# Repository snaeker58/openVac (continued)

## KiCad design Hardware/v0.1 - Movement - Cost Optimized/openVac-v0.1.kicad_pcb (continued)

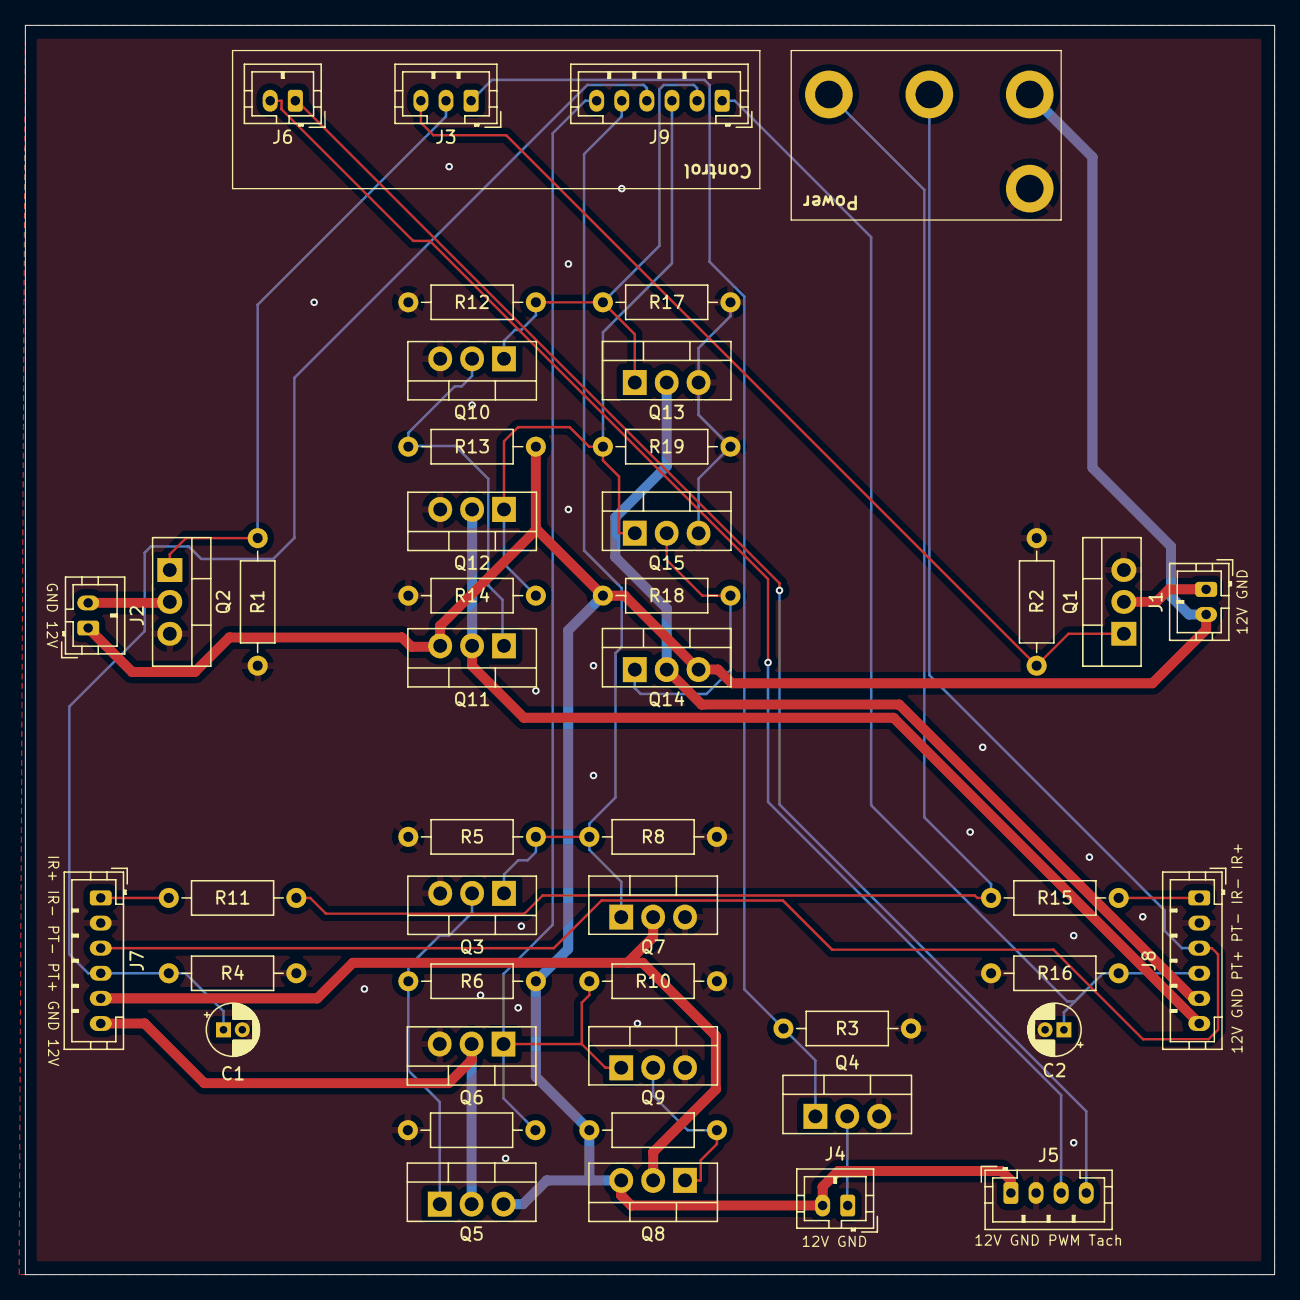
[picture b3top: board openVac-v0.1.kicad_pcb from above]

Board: 2 copper layers, 99.5 x 99.5 mm, 49 parts (0 on the bottom side), 28 nets.

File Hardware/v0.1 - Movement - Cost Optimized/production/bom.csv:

Designator,Footprint,Quantity,Value,LCSC Part #
"C1, C2",CP_Radial_D4.0mm_P1.50mm,2,0.1uF,
J1,JST_PH_B2B-PH-K_1x02_P2.00mm_Vertical,1,Brush Motor 2 (right),
J2,JST_PH_B2B-PH-K_1x02_P2.00mm_Vertical,1,Brush Motor 1 (left),
J3,JST_PH_B3B-PH-K_1x03_P2.00mm_Vertical,1,Brush Header (control),
J4,JST_PH_B2B-PH-K_1x02_P2.00mm_Vertical,1,Brush Motor Main,
J5,JST_PH_B4B-PH-K_1x04_P2.00mm_Vertical,1,Vacuum,
J6,JST_PH_B2B-PH-K_1x02_P2.00mm_Vertical,1,Vacuum Header (control),
J7,JST_PH_B6B-PH-K_1x06_P2.00mm_Vertical,1,Motor (left),
J8,JST_PH_B6B-PH-K_1x06_P2.00mm_Vertical,1,Motor (right),
J9,JST_PH_B6B-PH-K_1x06_P2.00mm_Vertical,1,Motor Header (control),
"Q1, Q10, Q12, Q13, Q15, Q2, Q3, Q4, Q6, Q7, Q9",TO-220-3_Vertical,11,IRF540N,
"Q11, Q14, Q5, Q8",TO-220-3_Vertical,4,IRF9540N,
"R1, R10, R12, R13, R14, R17, R18, R19, R2, R3, R5, R6, R7, R8, R9",R_Axial_DIN0207_L6.3mm_D2.5mm_P10.16mm_Horizontal,15,10k,
"R11, R15",R_Axial_DIN0207_L6.3mm_D2.5mm_P10.16mm_Horizontal,2,10,
"R16, R4",R_Axial_DIN0207_L6.3mm_D2.5mm_P10.16mm_Horizontal,2,5.1k,

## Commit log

2024-06-29 Circuit designs
2024-06-29 Documentation of the development process
2024-06-29 Additional session, fixed typo in session 4
2024-06-29 New session
2024-06-29 Fixed schematic mistake
2024-06-29 Fixed file name typo
2024-06-29 Added folder for better structure
2024-06-29 fix: mosfet orientation
2024-06-30 Added main library components in new software folder
2024-06-30 Added new session
2024-07-01 feat: all motors and main turbine wired in
2024-07-01 deleted backups from github
2024-07-02 Initial Github Desktop Sync
2024-07-03 Added new sessions
2024-07-03 new session added
2024-07-13 Session 13 hardware modifications
2024-07-13 Device resync (ignore)
2024-07-14 Phase v0.1 restructure
    This marks the end of the concept phase from now on every phase is supposed to be finalized with a prototype PCB. Each phase focusing on a specific aspect of the robot.
2024-07-18 Added session 14
2024-07-19 added session 15
2024-07-19 added session 16
2024-07-19 added missing files to session 16
2024-07-20 Github Desktop Backup
2024-07-21 added session 17
2024-07-21 added session 18
2024-07-21 added session 19
2024-07-23 added session 20
2024-07-28 Fix: Missing soldermask
2024-09-13 Recreated repo, because Github Desktop is ass
    So GitHub Desktop Added around 300MB in dead files...
2024-09-13 BMS/BCS Ordering Preparations
    Finished all ordering preparations, PCB in production.
2024-09-26 Production error fix
    Fixed a design error post production with the high current rail. Fuck me!
2024-09-29 BMS/BCS Board Modified
    Added System Connector
